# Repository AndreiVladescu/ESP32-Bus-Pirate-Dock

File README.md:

# ESP32-Bus-Pirate-Dock

Open-source carrier board for the Espressif ESP32-S3 DevKit, designed to complement the [ESP32-Bus-Pirate](https://github.com/geo-tp/ESP32-Bus-Pirate) project.

## Overview

ESP32-Bus-Pirate-Dock is a hardware dock/carrier board for the ESP32-S3 DevKit. It provides level and voltage translation between the 3.3V ESP32-S3 and external peripherals, with support for 1.8V, 3.3V, and 5V operation.

The design is intended to work with original ESP32-S3-DevKitC-1, as well as the wider devkit clones from third party suppliers.

## Hardware status

Current hardware revision: V3

The markings on the PCB for the serial number `V0-YYWW-XXXXX` are as follows: 
- version `0`
- year and week number when these PCBs were produced
- incrementing number of the current batch

An example PCB with these markings would be `V3-2613-00512`, where:
- version number is `3`
- the year is `2026`, and the week is `13`
- this is the `512th` PCB made in that respective week

## Repository contents

- `dock/kicad/` — KiCad design files
- `dock/gerbers/` — PCB fabrication outputs
- `dock/schematic.pdf` — exported schematic reference
- `dock/BOM.csv` — bill of materials
- `3d_models/` — 3D models for the dock and a WIP case
- `images/` — presentation images

## Open-source scope

This repository open-sources the dock hardware design, including:
- schematic and PCB layout source files
- fabrication outputs
- bill of materials
- project documentation and images included in this repository

## Required external parts

This project requires an **ESP32-S3 DevKit to be procured separately by the end user**.

The ESP32-S3 DevKit is a third-party board/module and is **not included** as part of this hardware design repository unless explicitly stated. Vendor silicon, datasheets, trademarks, and separately licensed third-party materials remain the property of their respective owners.

These boards can be acquired through the official Espressif manufacturer and it's stores, or through other third-party websites. If not buying a genuine one,
make sure the dimensions fit one of the header pins on the board.

## PCB Design

### Top View

## Current Prototype

### Front Rendering

### Back Rendering

## Manufacturing and assembly

To fabricate the PCB, use the files in `dock/gerbers/`.

To inspect or modify the design, use the original KiCad source files in `dock/kicad/`.

To source components, use `dock/BOM.csv`.

## Case Design

The case for the ESP32 Bus Pirate Dock is still a work in progress. The current design uses two pieces, which can be printed using an FDM printer with
a 0.4 nozzle.

## License

Hardware design files in this repository are licensed under the CERN-OHL-W-2.0 license.
See [LICENSE](LICENSE) for the full license text.

Documentation and images in this repository are licensed under CC BY 4.0 unless otherwise noted.

Any third-party trademarks, datasheets, and separately licensed materials remain the property of their respective owners.

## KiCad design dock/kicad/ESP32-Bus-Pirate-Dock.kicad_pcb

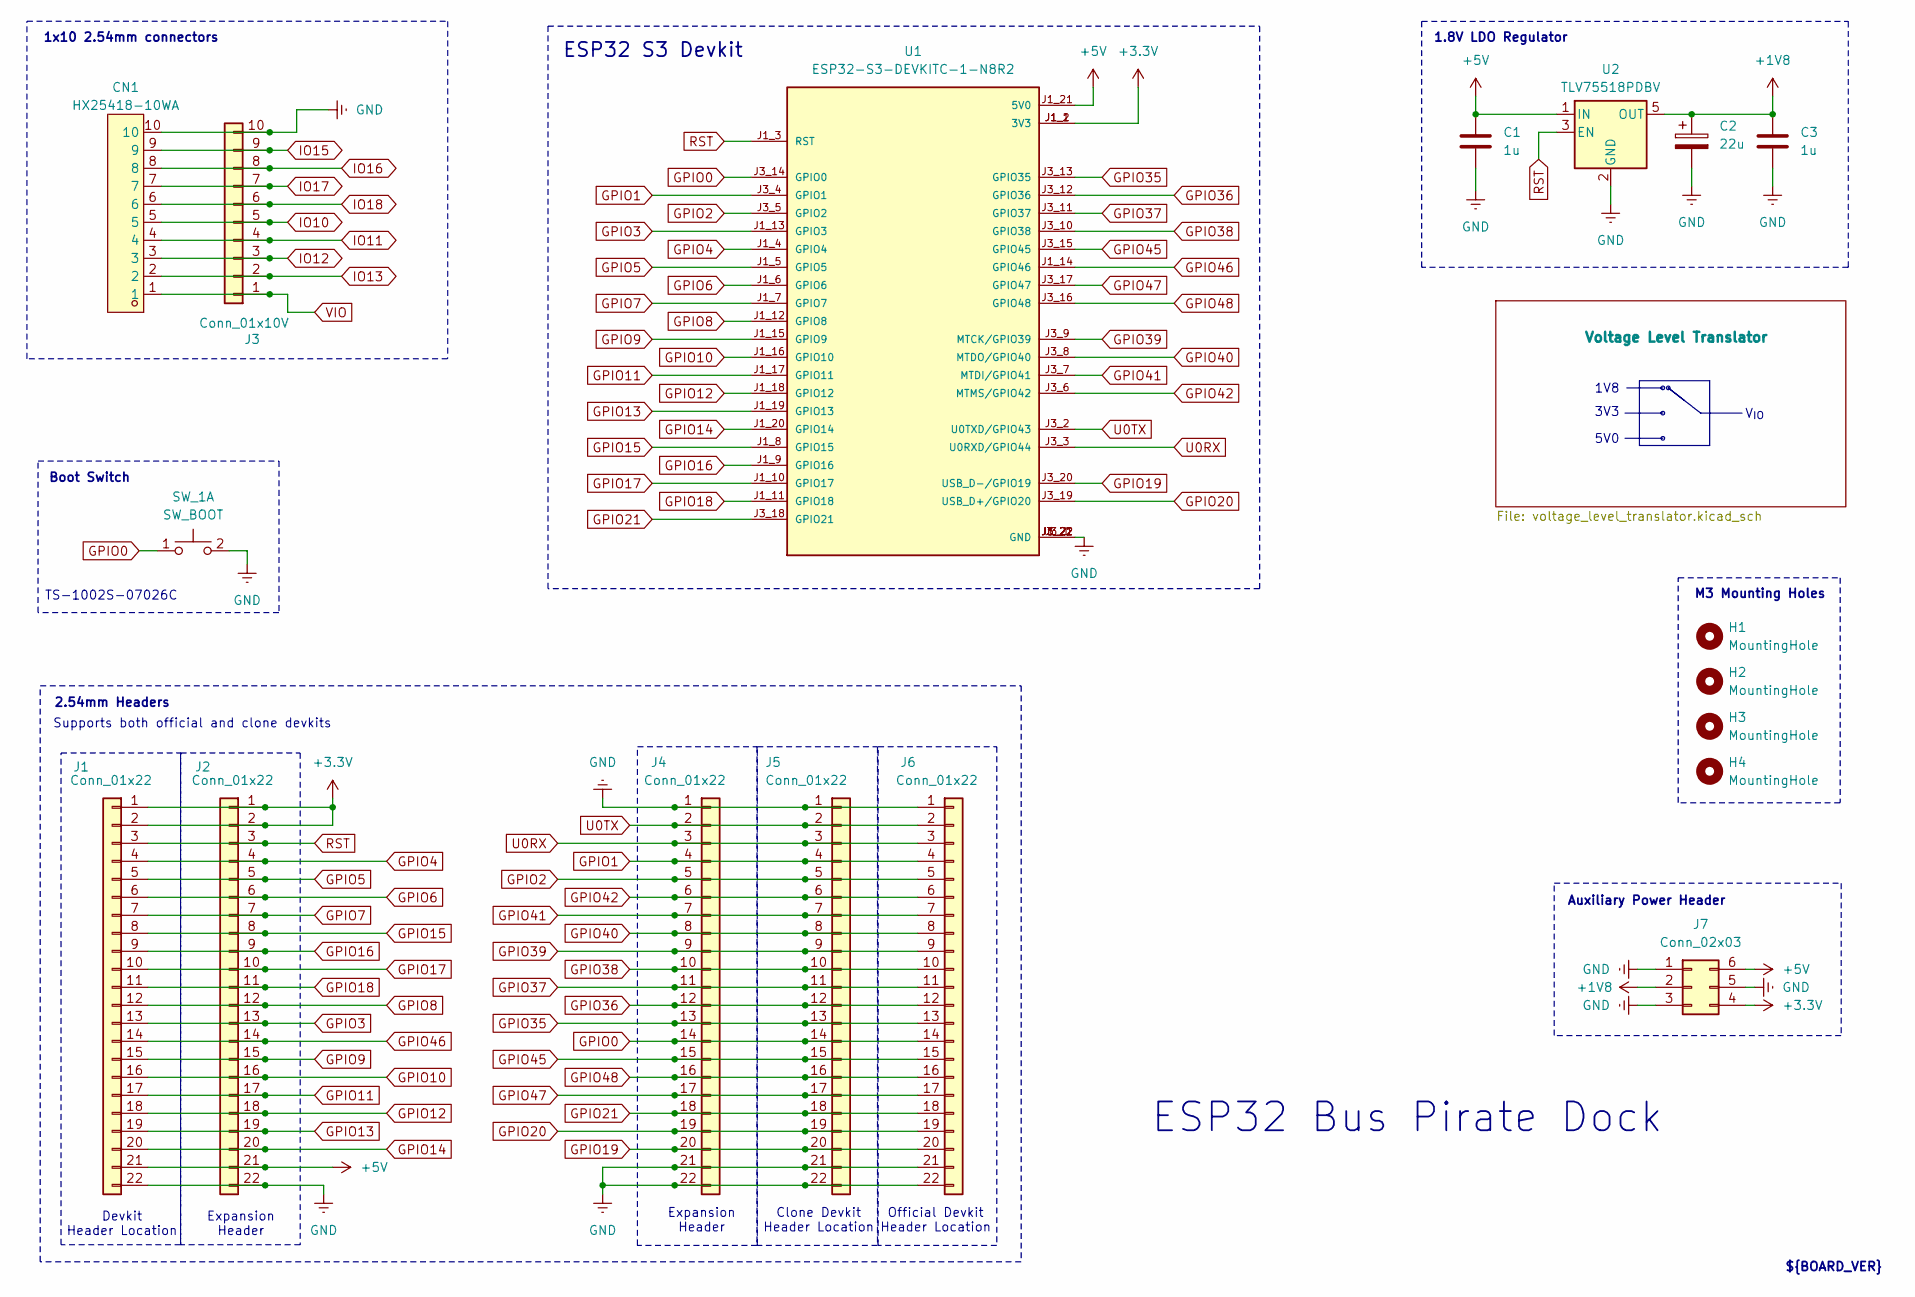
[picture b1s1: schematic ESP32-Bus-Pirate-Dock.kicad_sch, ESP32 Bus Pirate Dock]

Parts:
C1, C3: 1u; C_0805_2012Metric
C2: 22u; CP_Elec_5x4.5
CN1: HX25418-10WA; CONN-TH_HX25418-10WA; LCSC Part C704586
H1, H2, H3, H4: MountingHole; MountingHole_3.2mm_M3_DIN965_Pad_TopBottom
J1, J5, J6: Conn_01x22; PinSocket_1x22_P2.54mm_Vertical
J2, J4: Conn_01x22; PinHeader_1x22_P2.54mm_Vertical
J3: Conn_01x10V; PinSocket_1x10_P2.54mm_Vertical
J7: Conn_02x03; PinHeader_2x03_P2.54mm_Vertical
SW_1: SW_BOOT; SW_SPST_PTS645Sx43SMTR92
U1: ESP32-S3-DEVKITC-1-N8R2; XCVR_ESP32-S3-DEVKITC-1-N8R2; PARTREV V1
U2: TLV75518PDBV; SOT-23-5

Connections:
+1V8: C2.1, C3.1, J7.2, U2.5 (OUT); also elsewhere on the board
+3.3V: J1.1, J1.2, J2.1, J2.2, J7.4, U1.J1_1 (3V3), U1.J1_2 (3V3); also elsewhere on the board
+5V: C1.1, J1.21, J2.21, J7.6, U1.J1_21 (5V0), U2.1 (IN); also elsewhere on the board
GND: C1.2, C2.2, C3.2, CN1.10, J1.22, J2.22, J3.10, J4.1, J4.21, J4.22, J5.1, J5.21, J5.22, J6.1, J6.21, J6.22, J7.1, J7.3, J7.5, SW_1.2 (D), U1.J1_22 (GND), U1.J3_1 (GND), U1.J3_21 (GND), U1.J3_22 (GND), U2.2 (GND); also elsewhere on the board
GPIO0: J4.14, J5.14, J6.14, SW_1.1 (C), U1.J3_14 (GPIO0)
GPIO1: J4.4, J5.4, J6.4, U1.J3_4 (GPIO1)
GPIO2: J4.5, J5.5, J6.5, U1.J3_5 (GPIO2)
GPIO3: J1.13, J2.13, U1.J1_13 (GPIO3)
GPIO4: J1.4, J2.4, U1.J1_4 (GPIO4)
GPIO5: J1.5, J2.5, U1.J1_5 (GPIO5)
GPIO6: J1.6, J2.6, U1.J1_6 (GPIO6)
GPIO7: J1.7, J2.7, U1.J1_7 (GPIO7)
GPIO8: J1.12, J2.12, U1.J1_12 (GPIO8)
GPIO9: J1.15, J2.15, U1.J1_15 (GPIO9)
GPIO10: J1.16, J2.16, U1.J1_16 (GPIO10); also elsewhere on the board
GPIO11: J1.17, J2.17, U1.J1_17 (GPIO11); also elsewhere on the board
GPIO12: J1.18, J2.18, U1.J1_18 (GPIO12); also elsewhere on the board
GPIO13: J1.19, J2.19, U1.J1_19 (GPIO13); also elsewhere on the board
GPIO14: J1.20, J2.20, U1.J1_20 (GPIO14)
GPIO15: J1.8, J2.8, U1.J1_8 (GPIO15); also elsewhere on the board
GPIO16: J1.9, J2.9, U1.J1_9 (GPIO16); also elsewhere on the board
GPIO17: J1.10, J2.10, U1.J1_10 (GPIO17); also elsewhere on the board
GPIO18: J1.11, J2.11, U1.J1_11 (GPIO18); also elsewhere on the board
GPIO19: J4.20, J5.20, J6.20, U1.J3_20 (USB_D-/GPIO19)
GPIO20: J4.19, J5.19, J6.19, U1.J3_19 (USB_D+/GPIO20)
GPIO21: J4.18, J5.18, J6.18, U1.J3_18 (GPIO21)
GPIO35: J4.13, J5.13, J6.13, U1.J3_13 (GPIO35)
GPIO36: J4.12, J5.12, J6.12, U1.J3_12 (GPIO36)
GPIO37: J4.11, J5.11, J6.11, U1.J3_11 (GPIO37)
GPIO38: J4.10, J5.10, J6.10, U1.J3_10 (GPIO38)
GPIO39: J4.9, J5.9, J6.9, U1.J3_9 (MTCK/GPIO39)
GPIO40: J4.8, J5.8, J6.8, U1.J3_8 (MTDO/GPIO40)
GPIO41: J4.7, J5.7, J6.7, U1.J3_7 (MTDI/GPIO41)
GPIO42: J4.6, J5.6, J6.6, U1.J3_6 (MTMS/GPIO42)
GPIO45: J4.15, J5.15, J6.15, U1.J3_15 (GPIO45)
GPIO46: J1.14, J2.14, U1.J1_14 (GPIO46)
GPIO47: J4.17, J5.17, J6.17, U1.J3_17 (GPIO47)
GPIO48: J4.16, J5.16, J6.16, U1.J3_16 (GPIO48)
IO10: CN1.5, J3.5; also elsewhere on the board
IO11: CN1.4, J3.4; also elsewhere on the board
IO12: CN1.3, J3.3; also elsewhere on the board
IO13: CN1.2, J3.2; also elsewhere on the board
IO15: CN1.9, J3.9; also elsewhere on the board
IO16: CN1.8, J3.8; also elsewhere on the board
IO17: CN1.7, J3.7; also elsewhere on the board
IO18: CN1.6, J3.6; also elsewhere on the board
RST: J1.3, J2.3, U1.J1_3 (RST), U2.3 (EN)
U0RX: J4.3, J5.3, J6.3, U1.J3_3 (U0RXD/GPIO44)
U0TX: J4.2, J5.2, J6.2, U1.J3_2 (U0TXD/GPIO43)
VIO: CN1.1, J3.1; also elsewhere on the board

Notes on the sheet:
Boot Switch
M3 Mounting Holes
${BOARD_VER}
1.8V LDO Regulator
TS-1002S-07026C
1x10 2.54mm connectors
Auxiliary Power Header
Clone Devkit Header Location
Expansion Header
Official Devkit Header Location
2.54mm Headers
Devkit Header Location
5V0
3V3
ESP32 S3 Devkit
1V8
V_{IO}
Supports both official and clone devkits
ESP32 Bus Pirate Dock

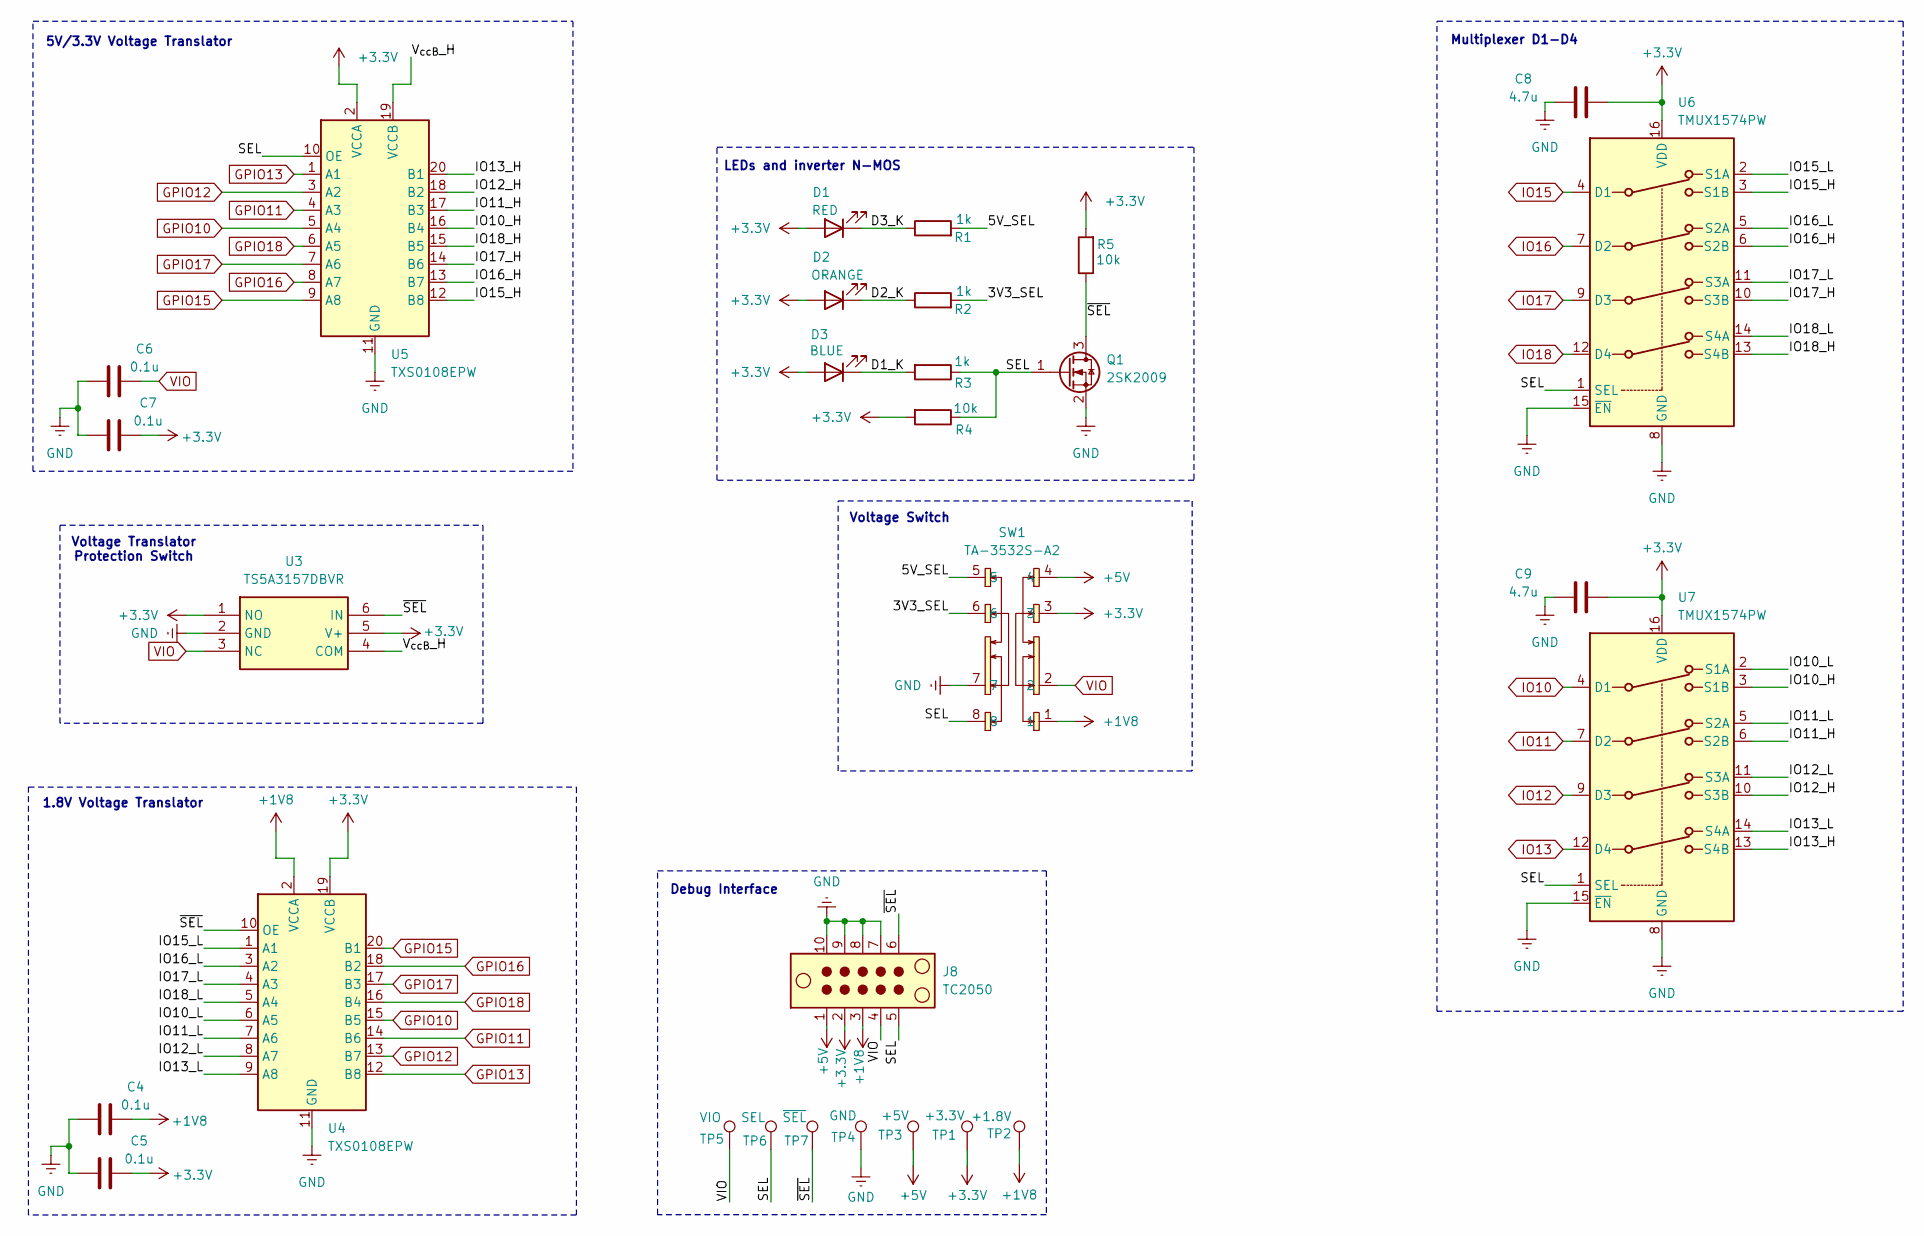
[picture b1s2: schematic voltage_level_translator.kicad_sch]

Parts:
C4, C5, C6, C7: 0.1u; C_0805_2012Metric
C8, C9: 4.7u; C_0805_2012Metric
D1: RED; LED_0805_2012Metric
D2: ORANGE; LED_0805_2012Metric
D3: BLUE; LED_0805_2012Metric
J8: TC2050; Tag-Connect_TC2050-IDC-NL_2x05_P1.27mm_Vertical_with_bottom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
Q1: 2SK2009; SOT-23
R1, R2, R3: 1k; R_0805_2012Metric
R4, R5: 10k; R_0805_2012Metric
SW1: TA-3532S-A2; SW-SMD_8P-L13.0-W3.5-P2.00; LCSC Part C514040
TP1: +3.3V; TestPoint_Pad_D1.0mm
TP2: +1.8V; TestPoint_Pad_D1.0mm
TP3: +5V; TestPoint_Pad_D1.0mm
TP4: GND; TestPoint_Pad_D1.0mm
TP5: VIO; TestPoint_Pad_D1.0mm
TP6: SEL; TestPoint_Pad_D1.0mm
TP7: ~{SEL}; TestPoint_Pad_D1.0mm
U3: TS5A3157DBVR; SOT95P280X145-6N; Mouser Part Number 595-TS5A3157DBVR
U4, U5: TXS0108EPW; Texas_PW0020A_TSSOP-20_4.4x6.5mm_P0.65mm
U6, U7: TMUX1574PW; TSSOP-16_4.4x5mm_P0.65mm

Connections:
+1V8: C4.1, J8.3, SW1.1, TP2.1, U4.2 (VCCA); also elsewhere on the board
+3.3V: C5.1, C7.1, C8.1, C9.1, D1.2 (A), D2.2 (A), D3.2 (A), J8.2, R4.2, R5.2, SW1.3, TP1.1, U3.1 (NO), U3.5 (V+), U4.19 (VCCB), U5.2 (VCCA), U6.16 (VDD), U7.16 (VDD); also elsewhere on the board
+5V: J8.1, SW1.4, TP3.1; also elsewhere on the board
/Voltage Level Translator/3V3_SEL: R2.2, SW1.6
/Voltage Level Translator/5V_SEL: R1.2, SW1.5
/Voltage Level Translator/D1_K: D3.1 (K), R3.2
/Voltage Level Translator/D2_K: D2.1 (K), R2.1
/Voltage Level Translator/D3_K: D1.1 (K), R1.1
/Voltage Level Translator/IO10_H: U5.16 (B4), U7.3 (S1B)
/Voltage Level Translator/IO10_L: U4.6 (A5), U7.2 (S1A)
/Voltage Level Translator/IO11_H: U5.17 (B3), U7.6 (S2B)
/Voltage Level Translator/IO11_L: U4.7 (A6), U7.5 (S2A)
/Voltage Level Translator/IO12_H: U5.18 (B2), U7.10 (S3B)
/Voltage Level Translator/IO12_L: U4.8 (A7), U7.11 (S3A)
/Voltage Level Translator/IO13_H: U5.20 (B1), U7.13 (S4B)
/Voltage Level Translator/IO13_L: U4.9 (A8), U7.14 (S4A)
/Voltage Level Translator/IO15_H: U5.12 (B8), U6.3 (S1B)
/Voltage Level Translator/IO15_L: U4.1 (A1), U6.2 (S1A)
/Voltage Level Translator/IO16_H: U5.13 (B7), U6.6 (S2B)
/Voltage Level Translator/IO16_L: U4.3 (A2), U6.5 (S2A)
/Voltage Level Translator/IO17_H: U5.14 (B6), U6.10 (S3B)
/Voltage Level Translator/IO17_L: U4.4 (A3), U6.11 (S3A)
/Voltage Level Translator/IO18_H: U5.15 (B5), U6.13 (S4B)
/Voltage Level Translator/IO18_L: U4.5 (A4), U6.14 (S4A)
/Voltage Level Translator/SEL: J8.5, Q1.1 (G), R3.1, R4.1, SW1.8, TP6.1, U5.10 (OE), U6.1 (SEL), U7.1 (SEL)
/Voltage Level Translator/V_{ccB}_H: U3.4 (COM), U5.19 (VCCB)
/Voltage Level Translator/~SEL: J8.6, Q1.3 (D), R5.1, TP7.1, U3.6 (IN), U4.10 (OE)
GND: C4.2, C5.2, C6.2, C7.2, C8.2, C9.2, J8.7, J8.8, J8.9, J8.10, Q1.2 (S), SW1.7, TP4.1, U3.2 (GND), U4.11 (GND), U5.11 (GND), U6.8 (GND), U6.15 (~EN), U7.8 (GND), U7.15 (~EN); also elsewhere on the board
GPIO10: U4.15 (B5), U5.5 (A4); also elsewhere on the board
GPIO11: U4.14 (B6), U5.4 (A3); also elsewhere on the board
GPIO12: U4.13 (B7), U5.3 (A2); also elsewhere on the board
GPIO13: U4.12 (B8), U5.1 (A1); also elsewhere on the board
GPIO15: U4.20 (B1), U5.9 (A8); also elsewhere on the board
GPIO16: U4.18 (B2), U5.8 (A7); also elsewhere on the board
GPIO17: U4.17 (B3), U5.7 (A6); also elsewhere on the board
GPIO18: U4.16 (B4), U5.6 (A5); also elsewhere on the board
IO10: U7.4 (D1); also elsewhere on the board
IO11: U7.7 (D2); also elsewhere on the board
IO12: U7.9 (D3); also elsewhere on the board
IO13: U7.12 (D4); also elsewhere on the board
IO15: U6.4 (D1); also elsewhere on the board
IO16: U6.7 (D2); also elsewhere on the board
IO17: U6.9 (D3); also elsewhere on the board
IO18: U6.12 (D4); also elsewhere on the board
VIO: C6.1, J8.4, SW1.2, TP5.1, U3.3 (NC); also elsewhere on the board

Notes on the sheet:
5V/3.3V Voltage Translator
Voltage Switch
LEDs and inverter N-MOS
Debug Interface
Voltage Translator Protection Switch
Multiplexer D1-D4
1.8V Voltage Translator

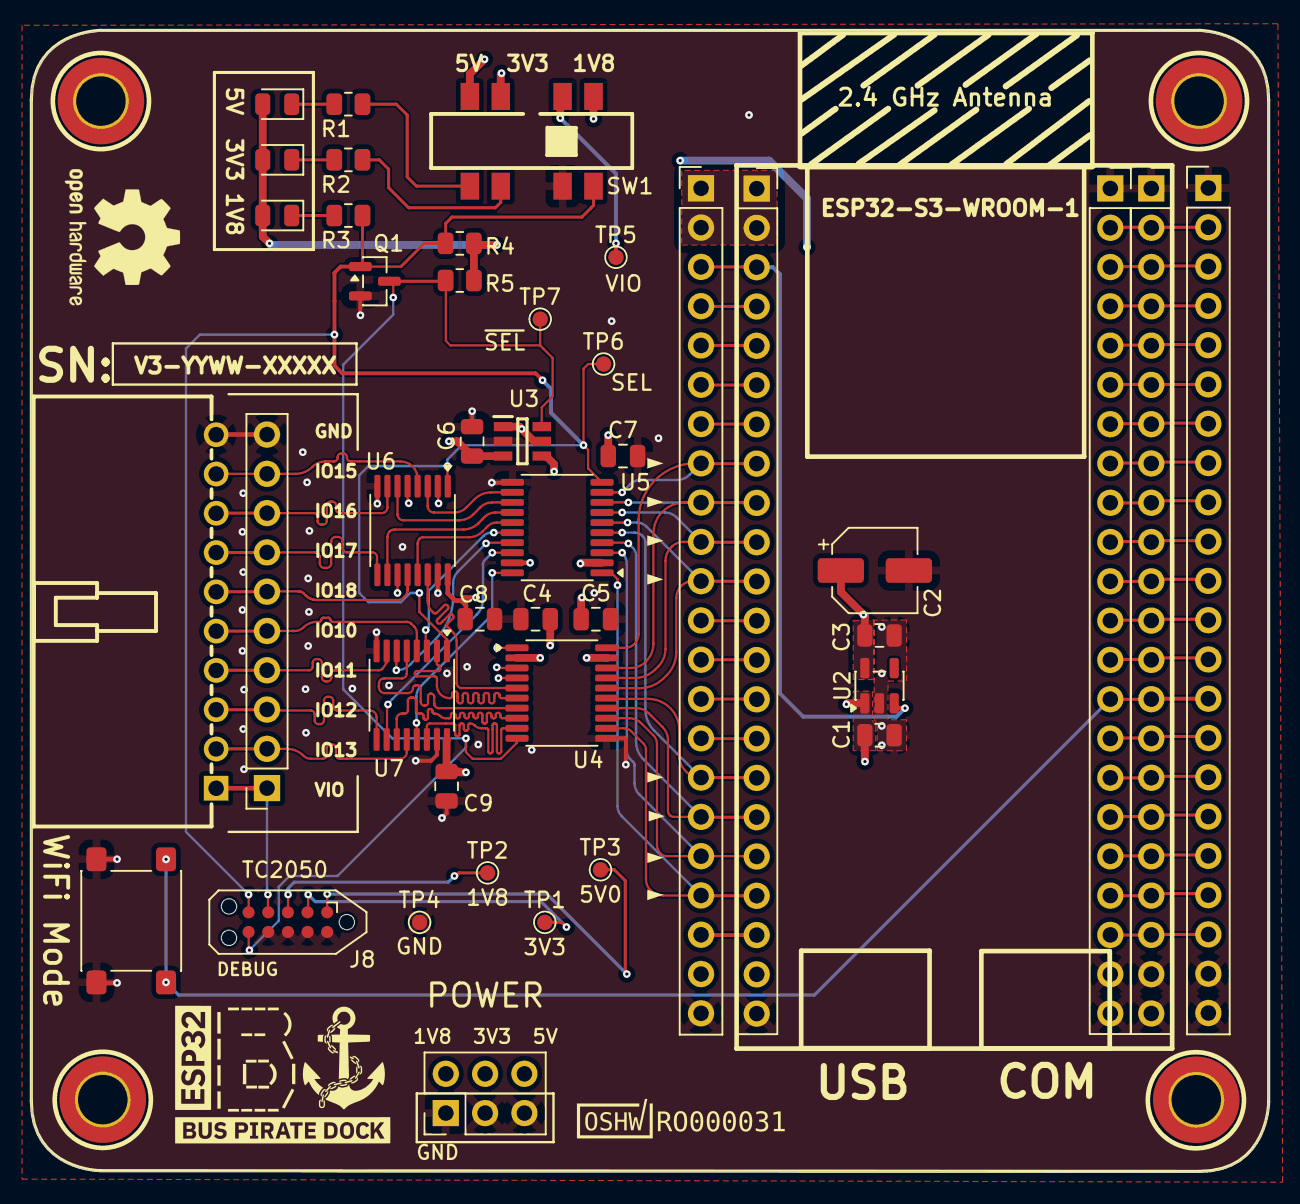
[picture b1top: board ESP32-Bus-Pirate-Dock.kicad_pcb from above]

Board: 4 copper layers, 80.0 x 73.8 mm, 46 parts (0 on the bottom side), 74 nets.

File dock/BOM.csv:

"Id";"Designator";"Footprint";"Quantity";"Designation";"Supplier and ref";
1;"SW_1";"SW_SPST_PTS645Sx43SMTR92";1;"SW_BOOT";;;
2;"D1";"LED_0805_2012Metric";1;"RED";;;
3;"C7,C5,C4,C6";"C_0805_2012Metric";4;"0.1u";;;
4;"C1,C3";"C_0805_2012Metric";2;"1u";;;
5;"C2";"CP_Elec_5x4.5";1;"22u";;;
6;"CN1";"CONN-TH_HX25418-10WA";1;"HX25418-10WA";;;
7;"J1,J6,J5";"PinSocket_1x22_P2.54mm_Vertical";3;"Conn_01x22";;;
8;"D2";"LED_0805_2012Metric";1;"ORANGE";;;
9;"J4,J2";"PinHeader_1x22_P2.54mm_Vertical";2;"Conn_01x22";;;
10;"U2";"SOT-23-5";1;"TLV75518PDBV";;;
11;"C9,C8";"C_0805_2012Metric";2;"4.7u";;;
12;"U3";"SOT95P280X145-6N";1;"TS5A3157DBVR";;;
13;"Q1";"SOT-23";1;"2N7002";;;
14;"R3,R1,R2";"R_0805_2012Metric";3;"1k";;;
15;"D3";"LED_0805_2012Metric";1;"BLUE";;;
16;"R5,R4";"R_0805_2012Metric";2;"10k";;;
17;"U7,U6";"TSSOP-16_4.4x5mm_P0.65mm";2;"TMUX1574PW";;;
18;"SW1";"SW-SMD_8P-L13.0-W3.5-P2.00";1;"TA-3532S-A2";;;
19;"U4,U5";"Texas_PW0020A_TSSOP-20_4.4x6.5mm_P0.65mm";2;"TXS0108EPW";;;
20;"J7";"PinHeader_2x03_P2.54mm_Vertical";1;"Conn_02x03";;;

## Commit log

2025-09-21 Added initial proto board
2025-09-22 File title changes
2025-09-24 Modified schematic and PCB
2025-09-24 Added 1.8V and another buttons
2025-09-26 Wired more
2025-09-27 Added logic level shifting
2025-09-27 PCB modifications
    - removed RESET switch
    - re-arranged FXMA108 pins
2025-09-27 PCB arrangement
2025-09-27 Added DP3T switch in schematic
2025-09-28 Added LEDs for voltage selection and DP3T switch
2025-09-28 Added logo
2025-09-28 First wiring attempt
2025-09-28 Excluded vertical header
2025-09-29 Added keyed connector
2025-09-29 Fully routed PCB prototype
2025-09-30 DRC Check Passed
2025-09-30 Fixed connector polarity
2025-10-01 Scheme organization
2025-10-02 Modified for PCBWay prototype
2025-10-05 PCBWay recommendation
2025-11-23 PCB reassignment
2025-11-23 Improved graphics
2025-11-23 Added switch 3D model
2025-11-23 Added separate power connector
2025-11-23 Updated power conn graphics
2025-11-24 Updated PCB & Logo
2025-11-24 Completed wiring for V2
2025-11-24 Removed blemishes
2025-11-24 Via & Ground pour touchups
2025-11-24 Added devkit
    Added official devkit for mockup
2025-11-28 Adapted board to unofficial and official devkit versions
2025-11-28 Updated schematic for hybrid devkit
2025-11-28 Updated schematic drawings
2025-11-28 Wired up LSF0108 Voltage Translator
2025-11-28 Eliminated FXMA108
2025-11-28 Added LSF1080 PCB placeholders
2025-11-30 Experimented with wiring
2025-11-30 Track length matching
2025-12-01 Updated PCB
2025-12-03 Fixed board outline
2025-12-07 Updated SEL Logic
2025-12-07 Eliminated old traces
2025-12-07 Updated wiring
2025-12-08 Partial re-wiring
2025-12-08 Wired everything
2025-12-11 Updated enable logic for translators
2025-12-11 Relabeled components
2025-12-15 Updated PCB to include TXS disabling
2025-12-15 Added DRC
2025-12-15 Reduced Logic circuit
2025-12-16 Changed track widths to 1.524mm
2025-12-17 Changed DP3T switch
2026-01-12 Updated graphics
2026-01-12 Revert "Updated graphics"
    This reverts commit d3577b9118030e223aebedf80b75efebfc92dd41.
2026-02-16 Modified voltage switching circuit
2026-02-17 Added the inverter N-MOS
2026-02-18 Changed LDO to TLV75518
2026-02-18 Modified PCB
    - Added Keepout rule for Devkit Antenna
    - Moved clone devkit header 0.2mm to better fit
2026-02-18 Minor pcb modifications
    - Modified capacitors for multiplexers to 4.7u
    - Added bypass capacitors near TXS0108EPW VCCA and VCCB
    - Changed some text on the main schematic
2026-02-20 Added Analog Switch
2026-02-20 New components PCB placement
2026-02-20 Negated switch OE
2026-02-20 Updated PCB placement
2026-02-24 Connected PCB
2026-02-24 Added board version
2026-02-24 Aesthetics update
2026-02-25 TS5A3157 SEL fixed
2026-02-26 Swapped pins for H translator
2026-02-26 Moved power traces on inner layer 2
2026-02-27 Changed PCB
    - Cosmetic silkscreen changes to width
    - Modified trace width of power lines to 0.508mm
2026-02-28 Mock arrangement
2026-03-08 Swapped 2N7002 for 2SK2009
2026-03-11 Added OSHW symbol + SN silkscreen
2026-03-11 Added board silkscreen outlines
2026-03-14 Modified renderings
2026-03-14 Reorganized project
2026-03-15 Modified license from MIT to CERN-OHL-W-2.0
2026-03-15 OSHWA compliance modifications
2026-03-15 Moved .gitignore
2026-03-15 Added BOM
2026-03-15 Added documentation license
2026-03-15 Added 3D models
    - dock
    - design files for case
    - binary stls for printing
2026-03-15 Document 3D models directory in README
2026-03-15 Added versioning numbering in README
2026-03-15 Added 3D model in README
2026-03-17 Added layer colors & updated board version
2026-03-17 Updated 3D Models
2026-03-17 Added assembly.gif
2026-03-17 Added .step files for case
2026-03-18 Added LCSC Parts & Board Version to v3
2026-03-18 Added testpoints, J3 mirrored
    - J3 mirrored in order to share the same pin numbers with CN1. It just makes it less confusing.
    - Added test points on power supplies, and SEL signals just to help test the board.
2026-03-19 Modified test pads & added TC2050
2026-03-19 Changed VTarget to Vio
2026-03-20 Re-added "Open Hardware" Logo
2026-03-29 Added the OSHW certification in README.md
2026-03-30 Added OSHW mark
2026-04-01 ESP32 C5 devkit addon
2026-04-02 Code refactoring
2026-04-08 Added PCB dimensions
2026-04-08 Minor schematic changes
    - Added net classes
    - Added cosmetic changes
2026-04-08 Impedance matching on translated pins
2026-04-09 Length matching on translated pins
